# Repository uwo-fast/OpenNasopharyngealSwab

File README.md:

# Open Source Nasopharyngeal Swab and UV Curing System

This repository hosts the open-source design files, instructions, and validation results for a parametric nasopharyngeal swab and UV curing system. The designs are tailored for distributed manufacturing using accessible 3D printing technologies. Originally developed to address swab shortages during the COVID-19 pandemic, this project aims to provide a low-cost, scalable solution for clinical testing and other medical applications.

## Features

- **Parametric Design:** Fully customizable in OpenSCAD to adapt swab and handle features for specific needs.
  - Tested with [github.com/CameronBrooks11/OpenSCAD-Batch-Export](https://github.com/CameronBrooks11/OpenSCAD-Batch-Export)
- **Distributed Manufacturing:** Designed for SLA 3D printers and modular UV curing systems, enabling local production with low-cost, accessible equipment.
- **Validated Performance:** Mechanical testing ensures durability and safety for clinical applications.
- **Open Source:** Licensed under GNU GPL v3.0 and CERN OHL v1.2 for maximum accessibility and collaboration.

## Cost Overview

- Nasopharyngeal Swabs:
  - Press-fit handle: ~$0.06/swab
  - Tong-style handle: ~$0.11/swab
- Modular UV Curing System: $45 total

## Included Components

1. **Swab Design Files:**
   - Parametric OpenSCAD files for the swab and handle.
   - STL files for SLA and FFF printers.
2. **UV Curing System:**
   - Design files for modular PCBs and 3D printable components.
   - Assembly instructions and parts list.

## Bill of Materials (BOM)

- **Swabs:** UV resin for swab heads and thermoplastics (e.g., PLA, PETG) for handles.
- **UV System:** Modular PCB components, UV LEDs, 3D printed brackets, and power supply.

## How to Use

### Swab Fabrication

1. Print swab heads using SLA 3D printers.
2. Print handles using FFF 3D printers.
3. Assemble and cure swabs in the UV curing system.

### UV Curing System Assembly

1. Solder PCBs and assemble the modular curing box.
2. Connect power and ensure system functionality with a multimeter.

### Validation

- Follow the provided mechanical testing protocols for tensile strength and break points.
- Conduct clinical testing in accordance with FDA or regional guidelines.

## Licensing

This project is licensed under:

- GNU General Public License (GPL) v3.0
- CERN Open Hardware License (OHL) v1.2

## Contributing

Contributions to improve the design, validation, or documentation are welcome. Please open an issue or submit a pull request.

## Citation

If you use this project in your work, please cite the original paper:  
Gallup, N., Pringle, A. M., Oberloier, S., Tanikella, N. G., & Pearce, J. M. (2020). *Parametric nasopharyngeal swab for sampling COVID-19 and other respiratory viruses: Open source design, SLA 3-D printing and UV curing system*. HardwareX, 8, e00135.

## Acknowledgments

This work was supported by the Witte Foundation and benefited from the contributions of numerous collaborators listed in the publication.

For more details, visit the [source paper](https://doi.org/10.1016/j.ohx.2020.e00135) or access original files on the [Open Science Framework (OSF)](https://osf.io/z5jgu/).

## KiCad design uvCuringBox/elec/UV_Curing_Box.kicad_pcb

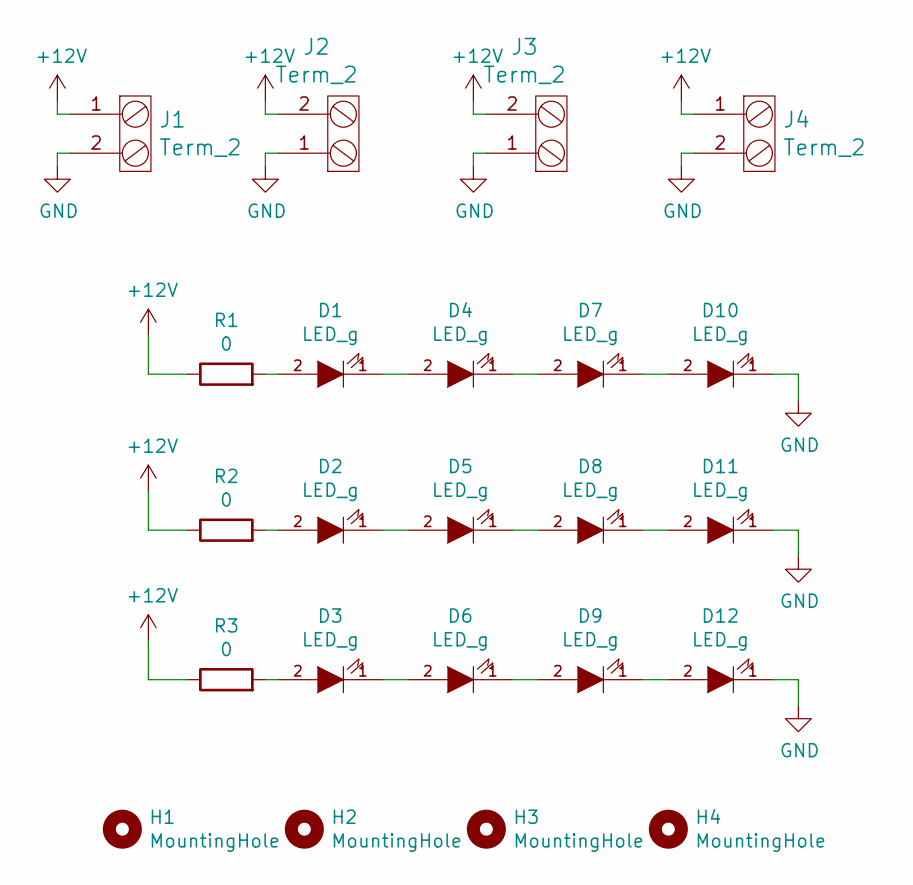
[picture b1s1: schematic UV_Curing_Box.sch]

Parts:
D1, D2, D3, D4, D5, D6, D7, D8, D9, D10, D11, D12: LED_g; LED-5MM; Part # C566C-GFF-CX0Y0892
H1, H2, H3, H4: MountingHole; MountingHole_2.2mm_M2
J1, J2, J3, J4: Term_2; TerminalBlock_Pheonix_MKDS1.5-2pol; Part # 1935161
R1, R2, R3: 0; R_1206_HandSoldering; Part # RC1206JR-070RL

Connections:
+12V: J1.1, J2.2, J3.2, J4.1, R1.1, R2.1, R3.1
GND: D10.1 (K), D11.1 (K), D12.1 (K), J1.2, J2.1, J3.1, J4.2
unnamed: D1.1 (K), D4.2 (A)
unnamed: D1.2 (A), R1.2
unnamed: D2.1 (K), D5.2 (A)
unnamed: D2.2 (A), R2.2
unnamed: D3.1 (K), D6.2 (A)
unnamed: D3.2 (A), R3.2
unnamed: D4.1 (K), D7.2 (A)
unnamed: D5.1 (K), D8.2 (A)
unnamed: D6.1 (K), D9.2 (A)
unnamed: D7.1 (K), D10.2 (A)
unnamed: D8.1 (K), D11.2 (A)
unnamed: D9.1 (K), D12.2 (A)

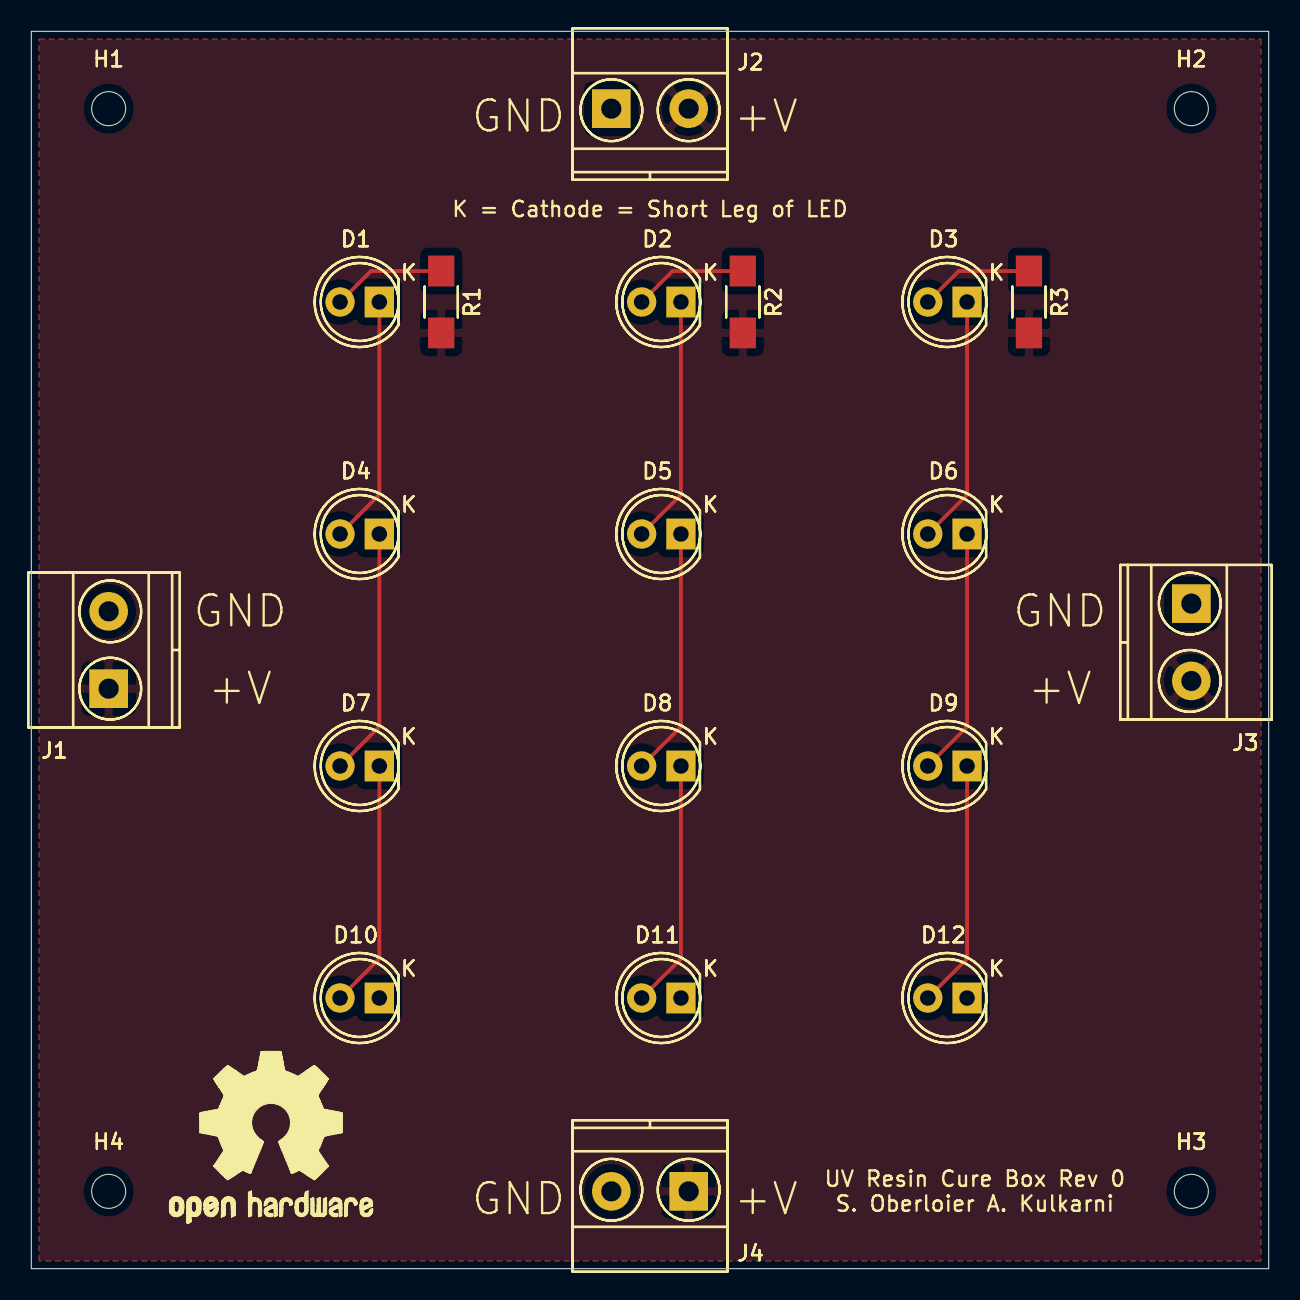
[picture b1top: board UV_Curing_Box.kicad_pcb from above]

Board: 2 copper layers, 80.0 x 80.0 mm, 23 parts (0 on the bottom side), 14 nets.

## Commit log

2024-12-01 fixed depreciated use of assign()
2024-12-01 updated to be compatible and test with OBE
2025-01-14 fixed index image
